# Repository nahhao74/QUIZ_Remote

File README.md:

<div align="center">

# Quiz Remote · ClassPulse

**A wireless classroom quiz system: battery-powered ESP32 answer pads, an MQTT broker and a live teacher dashboard.**

</div>

---

## Overview

Every student holds a small pad with 16 keys and two 7-segment digits. The teacher opens a session on a laptop, students type the 6-digit room code, and answers arrive on the projector within a fraction of a second. The whole system runs on the classroom Wi-Fi or a phone hotspot — no Internet connection is required.

| | |
|---|---|
| **Zero standby current** | A key press switches the board on; the ESP32 holds its own power and cuts it completely when done |
| **Reliable delivery** | MQTT QoS 1, an application-level ACK, retries and server-side de-duplication — no answer is lost or counted twice |
| **Network setup without reflashing** | Hold `0` for 3 s and the pad opens a captive-portal Wi-Fi setup page for any phone |
| **Live results** | Answer counts and the A–D distribution update in real time; correct answers stay hidden until the question closes |
| **Item analysis** | Difficulty, discrimination index, distractor effectiveness and KR-20 reliability after every session |
| **Question import** | Word, Excel, PDF and TXT, with optional AI help to write and review questions |

## The device

<table>
<tr>
<td align="center" width="28%"></td>
<td align="center" width="44%"></td>
<td align="center" width="28%"></td>
</tr>
<tr>
<td align="center"><sub>Showing a final score of 10</sub></td>
<td align="center"><sub>3D-printed enclosure, 16 keys, two 7-segment digits</sub></td>
<td align="center"><sub>Inside: the PCB and the 2 × AAA holder</sub></td>
</tr>
</table>

## The teacher app

<table>
<tr>
<td width="50%"></td>
<td width="50%"></td>
</tr>
<tr>
<td align="center"><sub>Presentation view after a question closes: correct answer, explanation and the A–D chart</sub></td>
<td align="center"><sub>Dashboard: question sets, AI assistant, exams, classes and session history</sub></td>
</tr>
<tr>
<td width="50%"></td>
<td width="50%"></td>
</tr>
<tr>
<td align="center"><sub>Session control: room code, question controls and every student's status in real time</sub></td>
<td align="center"><sub>End-of-session report: participation, accuracy and per-question results, with CSV export</sub></td>
</tr>
</table>

The interface is in Vietnamese.

## How it works

```mermaid
flowchart LR
  subgraph Classroom["Classroom LAN (Wi-Fi 2.4 GHz)"]
    P1[ESP32 pad]:::dev
    P2[ESP32 pad]:::dev
    P3[ESP32 pad ×N]:::dev
  end
  subgraph Laptop["Teacher laptop · Docker Compose"]
    M[(EMQX<br/>MQTT broker)]
    B[NestJS<br/>backend]
    D[(PostgreSQL)]
    W[React<br/>teacher app]
  end
  P1 & P2 & P3 -- "join / answer<br/>QoS 1" --> M
  M -- "ACK + retained room state" --> P1 & P2 & P3
  M <--> B
  B -- transaction --> D
  B -- Socket.IO --> W
  W -- REST --> B
  classDef dev fill:#fde7e4,stroke:#e7352c
```

One answer, end to end:

```mermaid
sequenceDiagram
  autonumber
  participant S as Student pad
  participant M as EMQX
  participant B as Backend
  participant D as PostgreSQL
  participant T as Teacher screen
  S->>M: answer (requestId, questionId, B, sequence)
  M->>B: deliver (QoS 1)
  B->>D: check room, deadline and sequence, then save answer and requestId in one transaction
  B-->>M: ack ANSWER_ACCEPTED
  M-->>S: ack (same requestId)
  B-->>T: session:update (counts, chart)
  Note over S,B: No ACK within 4 s → resend the identical message (up to 3 times).<br/>A repeated requestId returns the original result instead of saving twice.
```

## Hardware

<table>
<tr><td>

| Block | Function |
|---|---|
| **M1** | 2 × AAA cells, slide switch |
| **M2** | P-MOSFET power gate: key-press wake, GPIO13 self-hold |
| **M3** | MT3608 boost to 3.37 V on the 3V3 pin |
| **M4** | ESP32-WROOM-32 module in sockets |
| **M5** | 4 × 4 keypad (16 keys), also wakes the board |
| **M6** | 74HC595 + two 7-segment digits, multiplexed every 2 ms |

</td><td>

</td></tr>
</table>

<p align="center">&nbsp;&nbsp;&nbsp;<br><sub>The 52 × 90 mm two-layer board, front and back.</sub></p>

Schematic sheets, PCB, Gerber files, BOM and the full design rationale are in [`hardware/`](hardware/README.md) and the [design document](hardware/docs/design-document.md).

### What the digits show

| LED | Meaning | | LED | Meaning |
|:---:|---|---|:---:|---|
| `88` | Boot self-test | | `E1` | No Wi-Fi |
| `Ph` | Enter the room code | | `E2` | MQTT not connected |
| `Id` | Enter the student code | | `E3` | Rejected by the server |
| `On` | Connected to the server | | `E4` | Wrong number of digits |
| `01` | Question number | | `CF` | Wi-Fi setup page open |
| `A`…`d` | Selected answer | | `OF` | Powering off |

**Keys:** `1`–`4` choose A–D · `#` confirms · `*` deletes, or held 3 s powers off · `0` held 3 s opens Wi-Fi setup.

## Results

Measured with 50 simulated devices joining and answering at the same time, through the same broker and protocol as the real pads:

| Joined | Answers saved | Rejected / timed out | Duplicates saved twice | ACK latency p50 | p95 | max |
|:---:|:---:|:---:|:---:|:---:|:---:|:---:|
| **50 / 50** | **50 / 50** | **0** | **0** of 100 | **181 ms** | **371 ms** | **405 ms** |

The assembled board has completed a full quiz on two AAA cells over a phone hotspot. Full test report: [`web/docs/testing.md`](web/docs/testing.md).

## Repository layout

```text
.
├── hardware/                 KiCad 10 project, schematic PDFs/PNGs, Gerber, BOM, design document
│   ├── compact/              The current 52 × 90 mm board
│   ├── docs/                 Design document
│   └── tools/                PCB build script, ngspice wake/hold simulation, Wokwi sketch
├── firmware/                 Arduino sketches for the ESP32
│   ├── ClassPulseQuizDevice/       The quiz pad firmware (Wi-Fi, MQTT, power control, setup portal)
│   ├── ClassPulseKeypadDisplay/    Bring-up test: keypad → digits
│   └── ClassPulsePcbBreadboardTest/  Bring-up test: power latch, keys, segments, Wi-Fi
└── web/                      Server side, run with Docker Compose
    ├── apps/backend/         NestJS · Prisma · MQTT subscriber · REST · Socket.IO
    ├── apps/frontend/        React + Tailwind teacher app and presentation view
    ├── apps/device-simulator/  Browser pad simulator (MQTT over WebSocket)
    ├── packages/             Shared types and MQTT contracts (Zod)
    └── docs/                 Architecture, MQTT protocol, API, test report
```

## Quick start

**1. Server** (Docker with Compose v2):

```bash
cd web
cp .env.example .env          # fill in the <...> values
# set MQTT_TCP_BIND_ADDRESS to the laptop's Wi-Fi IP (hostname -I)
docker compose up --build -d
docker compose exec backend pnpm db:seed
```

Open **http://localhost:8080** and log in with the development account from the seed (see [`web/README.md`](web/README.md)).

**2. Device** (Arduino IDE, board *ESP32 Dev Module*): open `firmware/ClassPulseQuizDevice/ClassPulseQuizDevice.ino`, set `WIFI_SSID`, `WIFI_PASSWORD` and `MQTT_HOST` (the laptop's IP), then upload.

**3. Run a quiz:** start a session on the web → on the pad enter the room code `#`, a 2-digit student code `#` → answer with `1`–`4` and `#`.

> [!TIP]
> No spare pads? Add 30 simulated students to the same room:
> ```bash
> docker compose exec -e MQTT_URL=mqtt://emqx:1883 backend pnpm simulate --devices=30 --room=<room code>
> ```

> [!NOTE]
> The ESP32 only supports **2.4 GHz** Wi-Fi, and the pads and the laptop must be on the same network.

## Documentation

| Topic | Document |
|---|---|
| Board design, calculations, BOM | [hardware/README.md](hardware/README.md) · [design-document.md](hardware/docs/design-document.md) |
| Firmware configuration and usage | [firmware/ClassPulseQuizDevice/README.md](firmware/ClassPulseQuizDevice/README.md) |
| Server setup and features | [web/README.md](web/README.md) |
| System architecture and data model | [web/docs/architecture.md](web/docs/architecture.md) |
| MQTT topics, payloads, ACK codes | [web/docs/mqtt-protocol.md](web/docs/mqtt-protocol.md) |
| REST API and Socket.IO | [web/docs/api.md](web/docs/api.md) |
| Test report | [web/docs/testing.md](web/docs/testing.md) |

## License

Released under the [MIT License](LICENSE).

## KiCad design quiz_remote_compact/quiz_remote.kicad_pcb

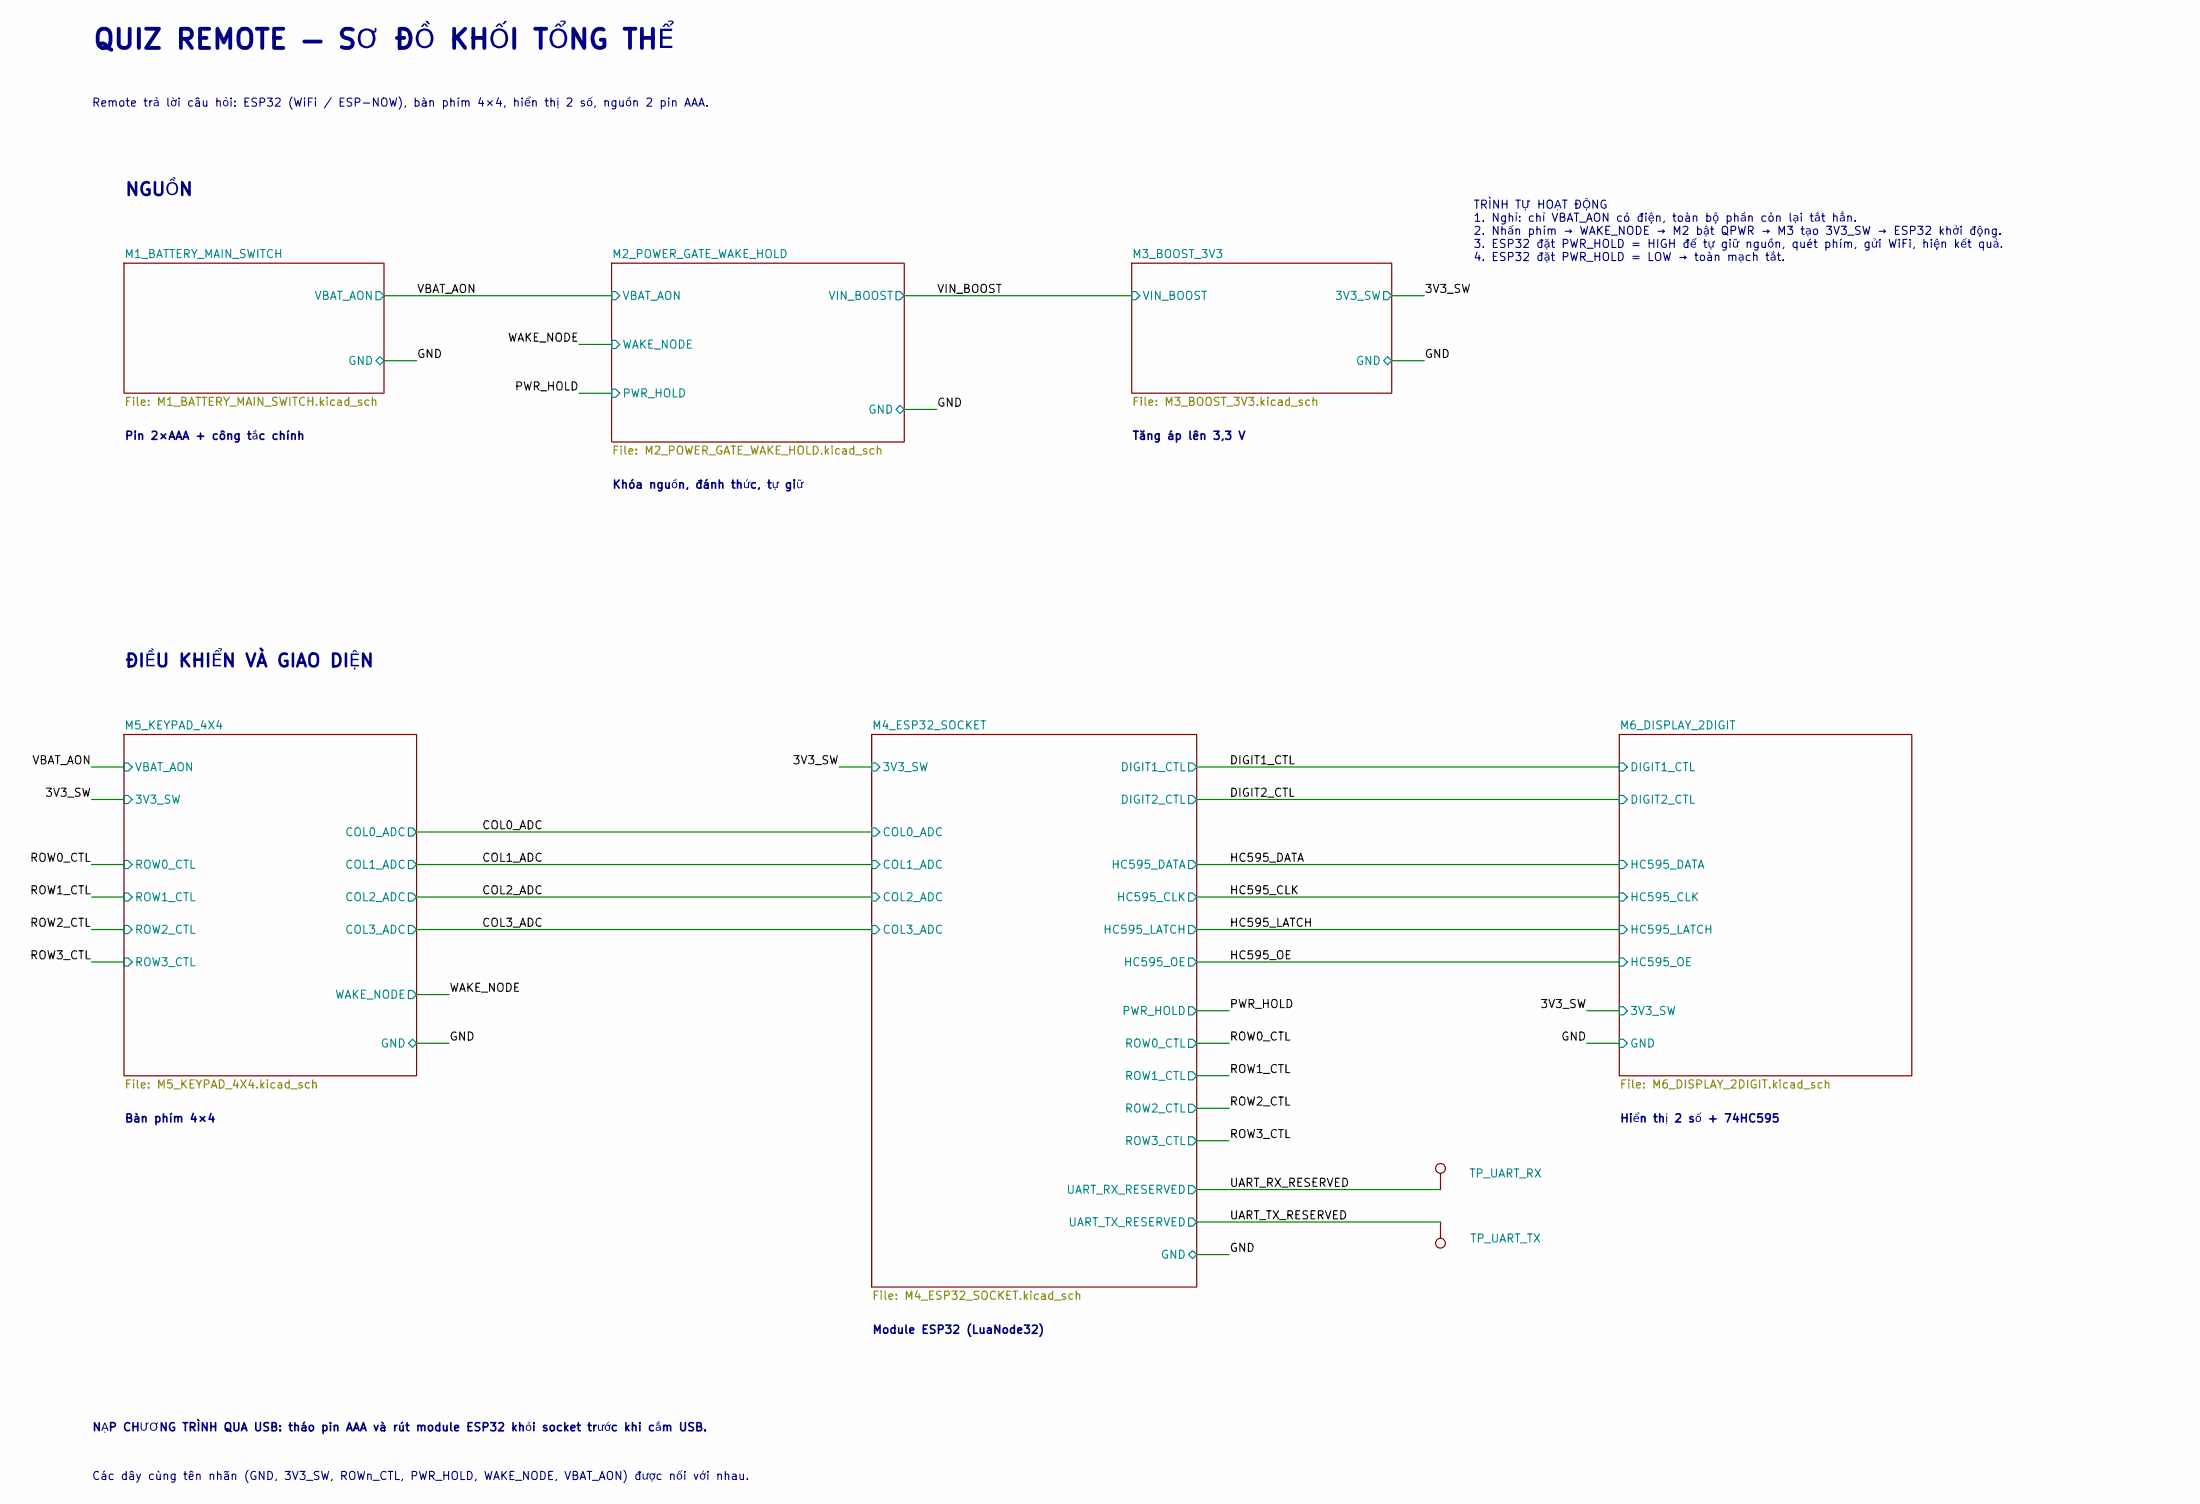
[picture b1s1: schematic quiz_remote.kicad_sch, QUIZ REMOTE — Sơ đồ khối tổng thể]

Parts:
TP_UART_RX: UART_RX_RESERVED; TestPoint_Pad_D1.5mm
TP_UART_TX: UART_TX_RESERVED; TestPoint_Pad_D1.5mm

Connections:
/UART_RX_RESERVED: TP_UART_RX.1; also elsewhere on the board
/UART_TX_RESERVED: TP_UART_TX.1; also elsewhere on the board

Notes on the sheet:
Pin 2×AAA + công tắc chính
Khóa nguồn, đánh thức, tự giữ
Tăng áp lên 3,3 V
Bàn phím 4×4
Module ESP32 (LuaNode32)
Hiển thị 2 số + 74HC595
QUIZ REMOTE — SƠ ĐỒ KHỐI TỔNG THỂ
Remote trả lời câu hỏi: ESP32 (WiFi / ESP-NOW), bàn phím 4×4, hiển thị 2 số, nguồn 2 pin AAA.
NGUỒN
ĐIỀU KHIỂN VÀ GIAO DIỆN
TRÌNH TỰ HOẠT ĐỘNG 1. Nghỉ: chỉ VBAT_AON có điện, toàn bộ phần còn lại tắt hẳn. 2. Nhấn phím → WAKE_NODE → M2 bật QPWR → M3 tạo 3V3_SW → ESP32 khởi động. 3. ESP32 đặt PWR_HOLD = HIGH để tự giữ nguồn, quét phím, gửi WiFi, hiện kết quả. 4. ESP32 đặt PWR_HOLD = LOW → toàn mạch tắt.
NẠP CHƯƠNG TRÌNH QUA USB: tháo pin AAA và rút module ESP32 khỏi socket trước khi cắm USB.
Các dây cùng tên nhãn (GND, 3V3_SW, ROWn_CTL, PWR_HOLD, WAKE_NODE, VBAT_AON) được nối với nhau.

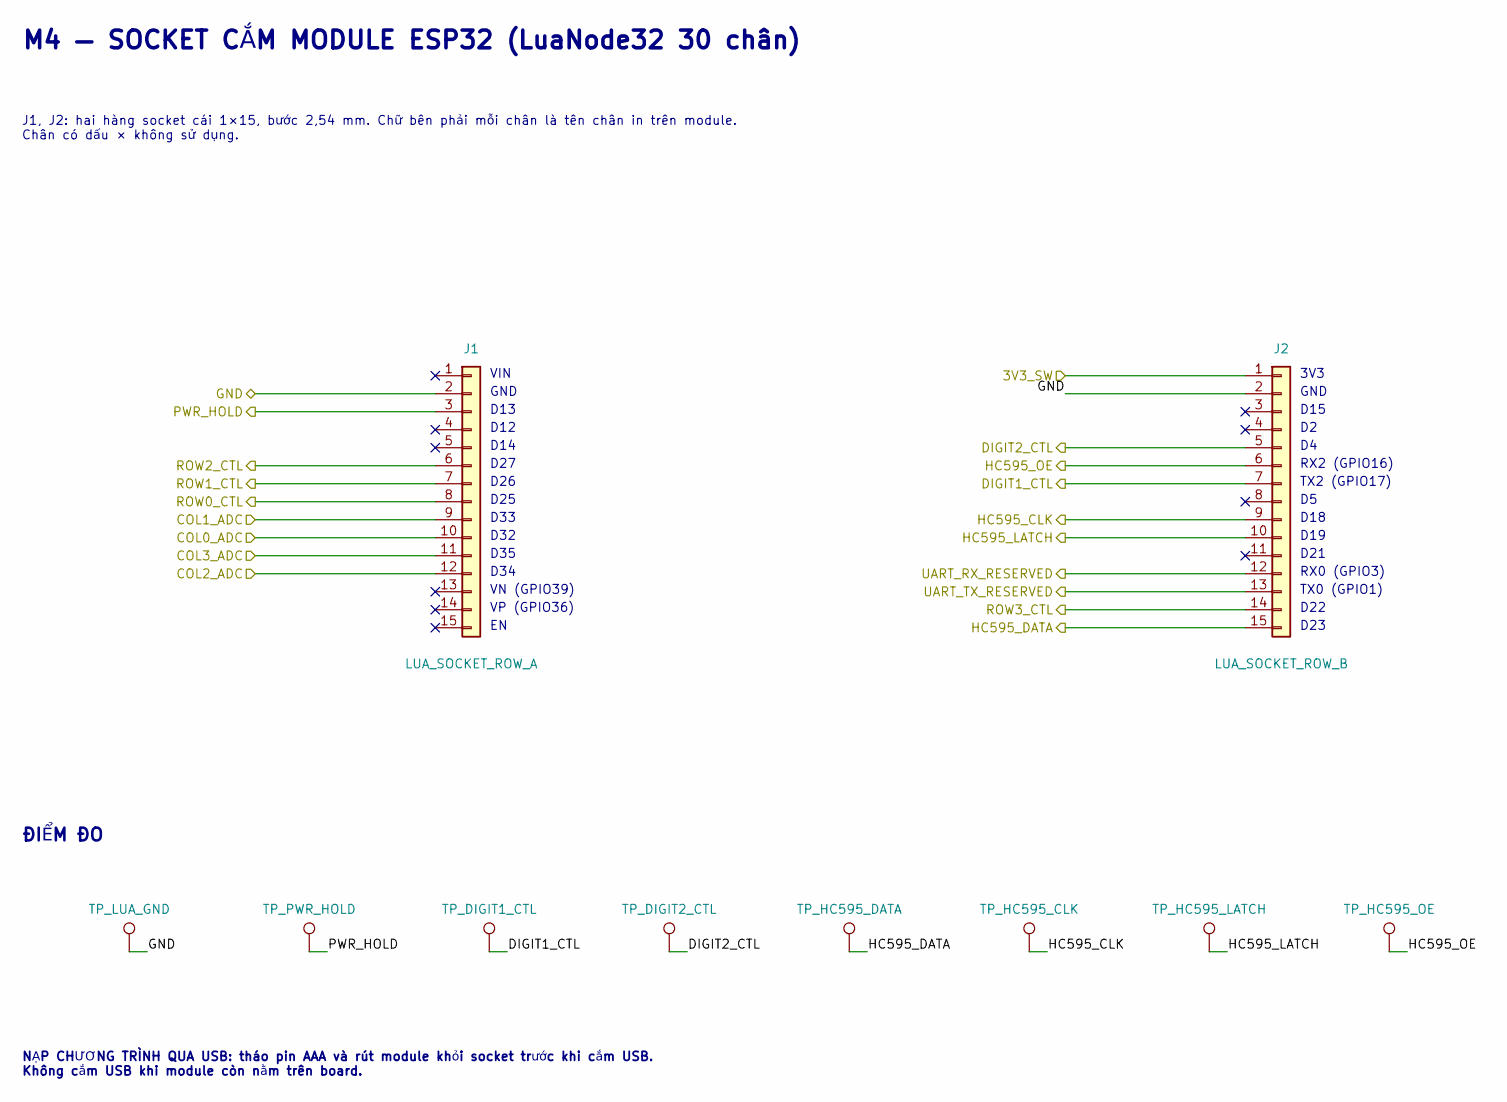
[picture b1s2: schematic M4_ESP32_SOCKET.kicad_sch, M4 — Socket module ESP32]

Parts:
J1: LUA_SOCKET_ROW_A; PinSocket_1x15_P2.54mm_Vertical; MPN 1x40_female_2.54_11.8_cut15
J2: LUA_SOCKET_ROW_B; PinSocket_1x15_P2.54mm_Vertical; MPN 1x40_female_2.54_11.8_cut15
TP_DIGIT1_CTL: DIGIT1_CTL; TestPoint_Pad_D1.5mm
TP_DIGIT2_CTL: DIGIT2_CTL; TestPoint_Pad_D1.5mm
TP_HC595_CLK: HC595_CLK; TestPoint_Pad_D1.5mm
TP_HC595_DATA: HC595_DATA; TestPoint_Pad_D1.5mm
TP_HC595_LATCH: HC595_LATCH; TestPoint_Pad_D1.5mm
TP_HC595_OE: HC595_OE; TestPoint_Pad_D1.5mm
TP_LUA_GND: GND; TestPoint_Pad_D1.5mm
TP_PWR_HOLD: PWR_HOLD; TestPoint_Pad_D1.5mm

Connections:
/3V3_SW: J2.1; also elsewhere on the board
/COL0_ADC: J1.10; also elsewhere on the board
/COL1_ADC: J1.9; also elsewhere on the board
/COL2_ADC: J1.12; also elsewhere on the board
/COL3_ADC: J1.11; also elsewhere on the board
/DIGIT1_CTL: J2.7, TP_DIGIT1_CTL.1; also elsewhere on the board
/DIGIT2_CTL: J2.5, TP_DIGIT2_CTL.1; also elsewhere on the board
/HC595_CLK: J2.9, TP_HC595_CLK.1; also elsewhere on the board
/HC595_DATA: J2.15, TP_HC595_DATA.1; also elsewhere on the board
/HC595_LATCH: J2.10, TP_HC595_LATCH.1; also elsewhere on the board
/HC595_OE: J2.6, TP_HC595_OE.1; also elsewhere on the board
/PWR_HOLD: J1.3, TP_PWR_HOLD.1; also elsewhere on the board
/ROW0_CTL: J1.8; also elsewhere on the board
/ROW1_CTL: J1.7; also elsewhere on the board
/ROW2_CTL: J1.6; also elsewhere on the board
/ROW3_CTL: J2.14; also elsewhere on the board
/UART_RX_RESERVED: J2.12; also elsewhere on the board
/UART_TX_RESERVED: J2.13; also elsewhere on the board

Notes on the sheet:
VIN
GND
D13
D12
D14
D27
D26
D25
D33
D32
D35
D34
VN (GPIO39)
VP (GPIO36)
3V3
D15
RX2 (GPIO16)
TX2 (GPIO17)
D18
D19
D21
RX0 (GPIO3)
TX0 (GPIO1)
D22
D23
M4 — SOCKET CẮM MODULE ESP32 (LuaNode32 30 chân)
J1, J2: hai hàng socket cái 1×15, bước 2,54 mm. Chữ bên phải mỗi chân là tên chân in trên module. Chân có dấu × không sử dụng.
ĐIỂM ĐO
NẠP CHƯƠNG TRÌNH QUA USB: tháo pin AAA và rút module khỏi socket trước khi cắm USB. Không cắm USB khi module còn nằm trên board.

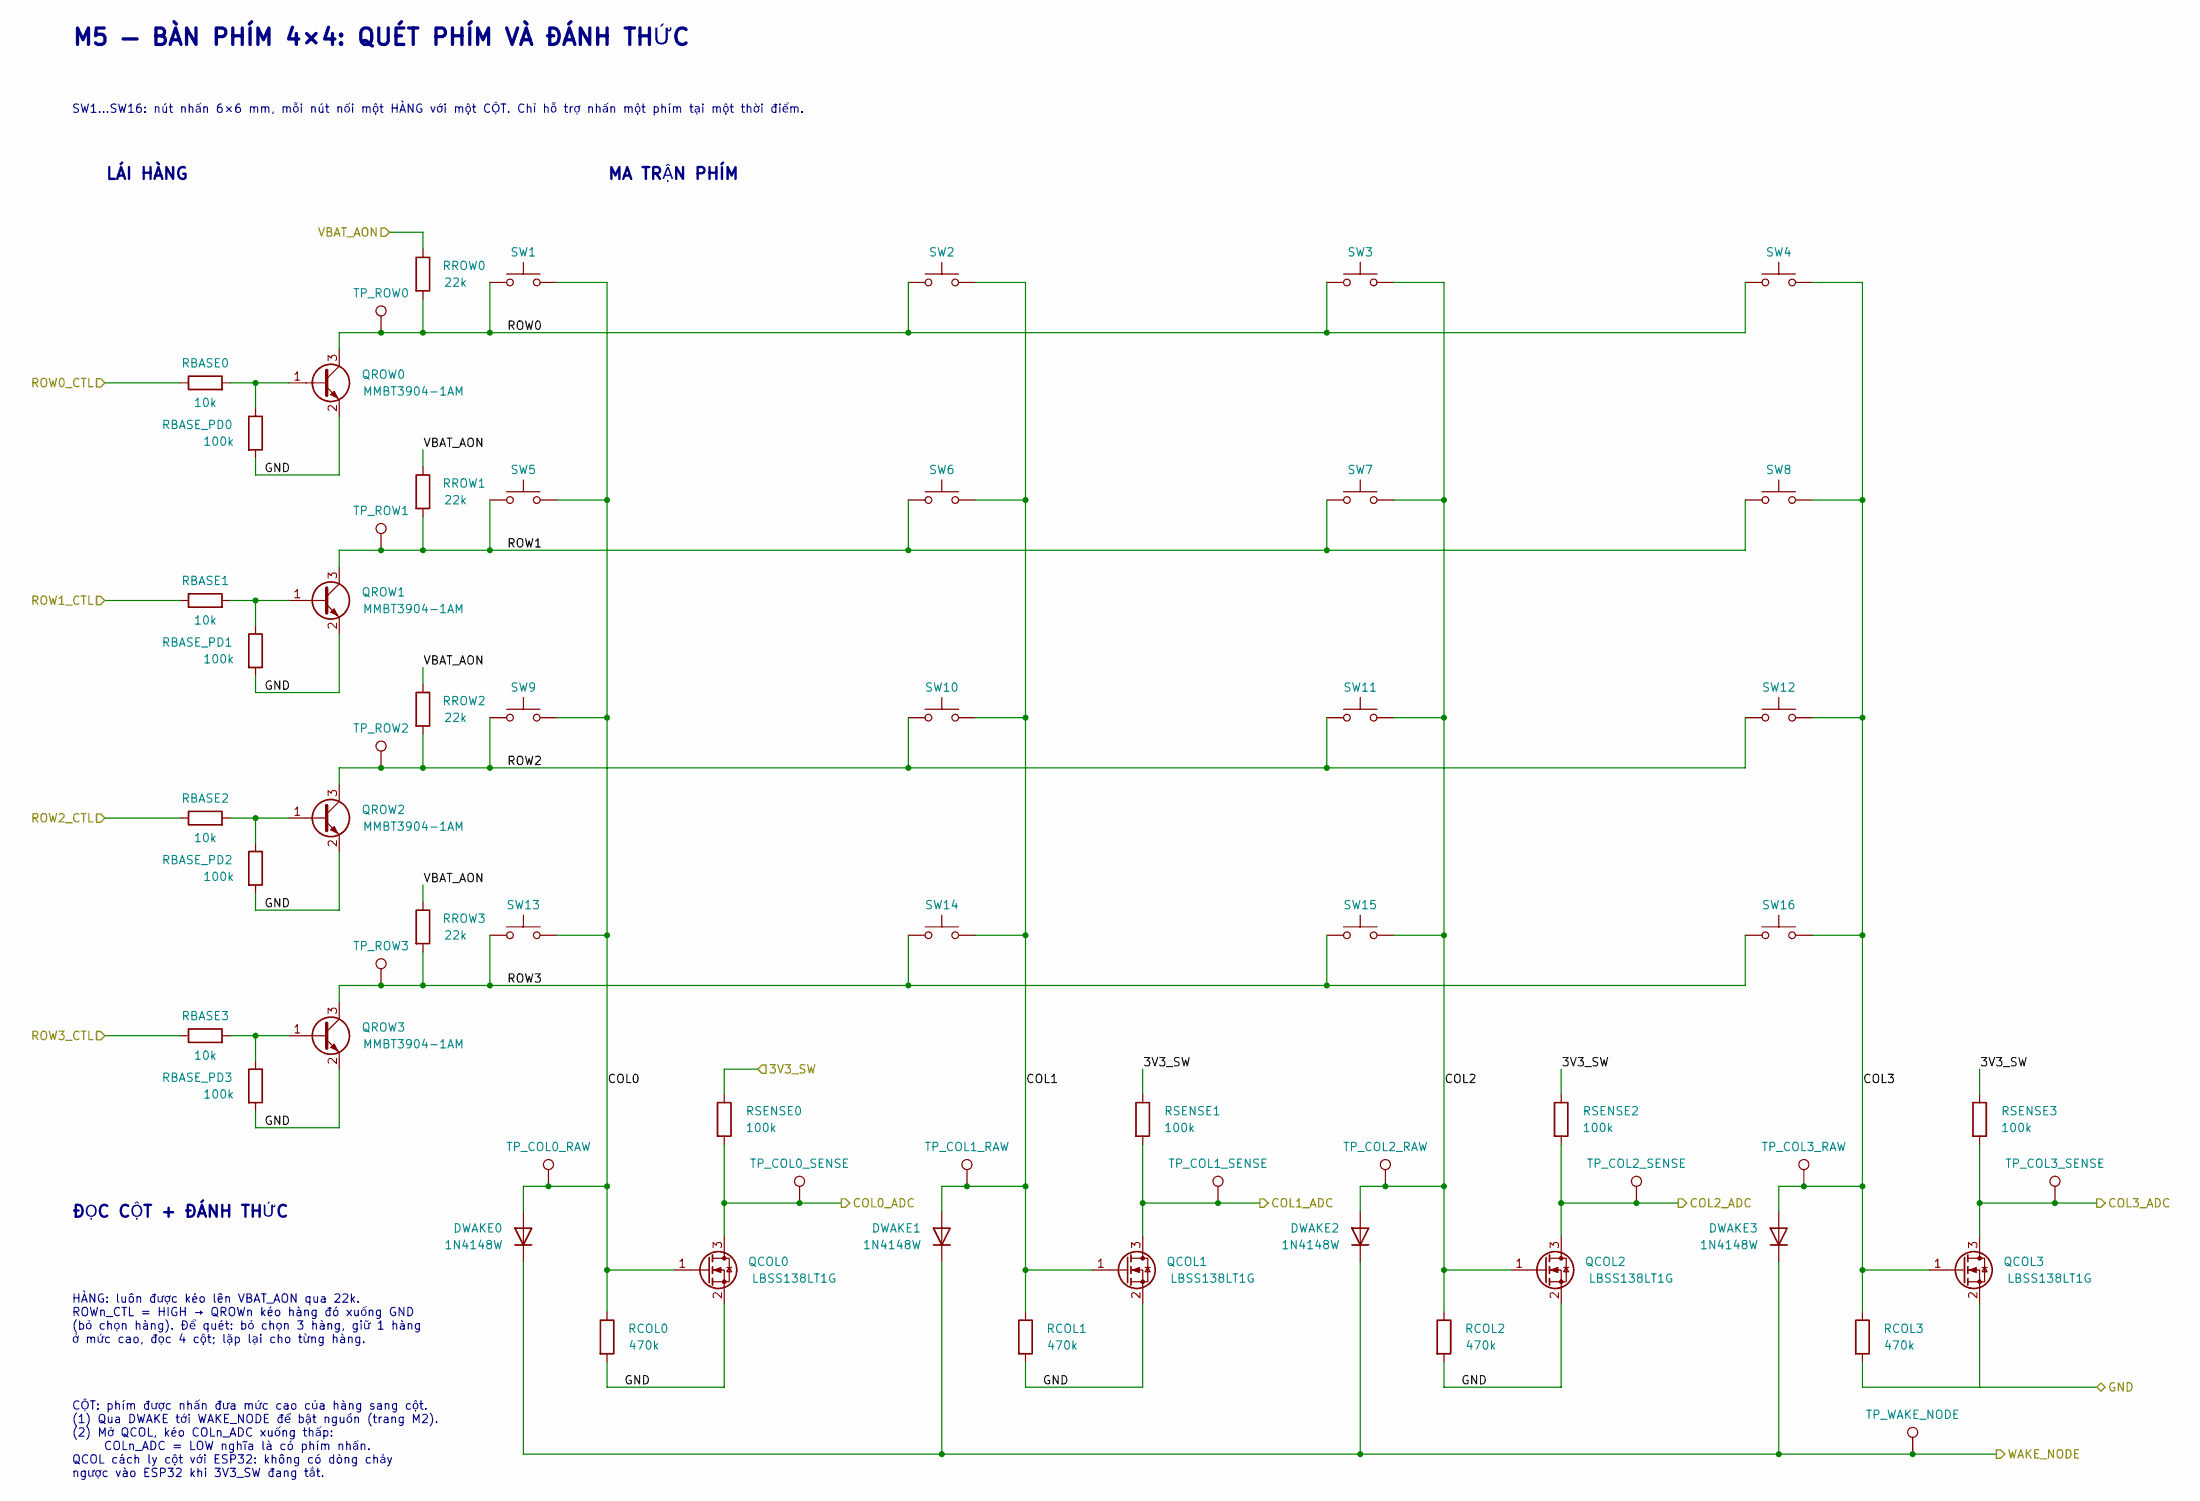
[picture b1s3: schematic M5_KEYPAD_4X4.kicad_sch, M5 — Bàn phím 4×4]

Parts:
DWAKE0, DWAKE1, DWAKE2, DWAKE3: 1N4148W; D_SOD-123; MPN 1N4148W-E3-18
QCOL0, QCOL1, QCOL2, QCOL3: LBSS138LT1G; SOT-23; MPN LBSS138LT1G
QROW0, QROW1, QROW2, QROW3: MMBT3904-1AM; SOT-23; MPN MMBT3904,215
RBASE0, RBASE1, RBASE2, RBASE3: 10k; R_0805_2012Metric; MPN RC0805FR-0710KL
RBASE_PD0, RBASE_PD1, RBASE_PD2, RBASE_PD3: 100k; R_0805_2012Metric; MPN RC0805FR-07100KL
RCOL0, RCOL1, RCOL2, RCOL3: 470k; R_0805_2012Metric; MPN RC0805FR-07470KL
RROW0, RROW1, RROW2, RROW3: 22k; R_0805_2012Metric; MPN RC0805FR-0722KL
RSENSE0, RSENSE1, RSENSE2, RSENSE3: 100k; R_0805_2012Metric; MPN RC0805FR-07100KL
SW1, SW2, SW3, SW4, SW5, SW6, SW7, SW8, SW9, SW10, SW11, SW12, SW13, SW14, SW15, SW16: 6x6_THT_NO; SW_6x6_H4.3_LK14489; MPN LK14489
TP_COL0_RAW: COL0; TestPoint_Pad_D1.5mm
TP_COL0_SENSE: COL0_ADC; TestPoint_Pad_D1.5mm
TP_COL1_RAW: COL1; TestPoint_Pad_D1.5mm
TP_COL1_SENSE: COL1_ADC; TestPoint_Pad_D1.5mm
TP_COL2_RAW: COL2; TestPoint_Pad_D1.5mm
TP_COL2_SENSE: COL2_ADC; TestPoint_Pad_D1.5mm
TP_COL3_RAW: COL3; TestPoint_Pad_D1.5mm
TP_COL3_SENSE: COL3_ADC; TestPoint_Pad_D1.5mm
TP_ROW0: ROW0; TestPoint_Pad_D1.5mm
TP_ROW1: ROW1; TestPoint_Pad_D1.5mm
TP_ROW2: ROW2; TestPoint_Pad_D1.5mm
TP_ROW3: ROW3; TestPoint_Pad_D1.5mm
TP_WAKE_NODE: WAKE_NODE; TestPoint_Pad_D1.5mm

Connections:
/3V3_SW: RSENSE0.1, RSENSE1.1, RSENSE2.1, RSENSE3.1; also elsewhere on the board
/COL0_ADC: QCOL0.3 (D), RSENSE0.2, TP_COL0_SENSE.1; also elsewhere on the board
/COL1_ADC: QCOL1.3 (D), RSENSE1.2, TP_COL1_SENSE.1; also elsewhere on the board
/COL2_ADC: QCOL2.3 (D), RSENSE2.2, TP_COL2_SENSE.1; also elsewhere on the board
/COL3_ADC: QCOL3.3 (D), RSENSE3.2, TP_COL3_SENSE.1; also elsewhere on the board
/M5_KEYPAD_4X4/COL0: DWAKE0.2 (A), QCOL0.1 (G), RCOL0.1, SW1.2, SW5.2, SW9.2, SW13.2, TP_COL0_RAW.1
/M5_KEYPAD_4X4/COL1: DWAKE1.2 (A), QCOL1.1 (G), RCOL1.1, SW2.2, SW6.2, SW10.2, SW14.2, TP_COL1_RAW.1
/M5_KEYPAD_4X4/COL2: DWAKE2.2 (A), QCOL2.1 (G), RCOL2.1, SW3.2, SW7.2, SW11.2, SW15.2, TP_COL2_RAW.1
/M5_KEYPAD_4X4/COL3: DWAKE3.2 (A), QCOL3.1 (G), RCOL3.1, SW4.2, SW8.2, SW12.2, SW16.2, TP_COL3_RAW.1
/M5_KEYPAD_4X4/ROW0: QROW0.3 (C), RROW0.2, SW1.1, SW2.1, SW3.1, SW4.1, TP_ROW0.1
/M5_KEYPAD_4X4/ROW1: QROW1.3 (C), RROW1.2, SW5.1, SW6.1, SW7.1, SW8.1, TP_ROW1.1
/M5_KEYPAD_4X4/ROW2: QROW2.3 (C), RROW2.2, SW9.1, SW10.1, SW11.1, SW12.1, TP_ROW2.1
/M5_KEYPAD_4X4/ROW3: QROW3.3 (C), RROW3.2, SW13.1, SW14.1, SW15.1, SW16.1, TP_ROW3.1
/ROW0_CTL: RBASE0.1; also elsewhere on the board
/ROW1_CTL: RBASE1.1; also elsewhere on the board
/ROW2_CTL: RBASE2.1; also elsewhere on the board
/ROW3_CTL: RBASE3.1; also elsewhere on the board
/VBAT_AON: RROW0.1, RROW1.1, RROW2.1, RROW3.1; also elsewhere on the board
/WAKE_NODE: DWAKE0.1 (K), DWAKE1.1 (K), DWAKE2.1 (K), DWAKE3.1 (K), TP_WAKE_NODE.1; also elsewhere on the board
unnamed: QROW0.1 (B), RBASE0.2, RBASE_PD0.1
unnamed: QROW1.1 (B), RBASE1.2, RBASE_PD1.1
unnamed: QROW2.1 (B), RBASE2.2, RBASE_PD2.1
unnamed: QROW3.1 (B), RBASE3.2, RBASE_PD3.1

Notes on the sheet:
M5 — BÀN PHÍM 4×4: QUÉT PHÍM VÀ ĐÁNH THỨC
SW1…SW16: nút nhấn 6×6 mm, mỗi nút nối một HÀNG với một CỘT. Chỉ hỗ trợ nhấn một phím tại một thời điểm.
LÁI HÀNG
MA TRẬN PHÍM
ĐỌC CỘT + ĐÁNH THỨC
HÀNG: luôn được kéo lên VBAT_AON qua 22k. ROWn_CTL = HIGH → QROWn kéo hàng đó xuống GND (bỏ chọn hàng). Để quét: bỏ chọn 3 hàng, giữ 1 hàng ở mức cao, đọc 4 cột; lặp lại cho từng hàng.
CỘT: phím được nhấn đưa mức cao của hàng sang cột. (1) Qua DWAKE tới WAKE_NODE để bật nguồn (trang M2). (2) Mở QCOL, kéo COLn_ADC xuống thấp: COLn_ADC = LOW nghĩa là có phím nhấn. QCOL cách ly cột với ESP32: không có dòng chảy ngược vào ESP32 khi 3V3_SW đang tắt.

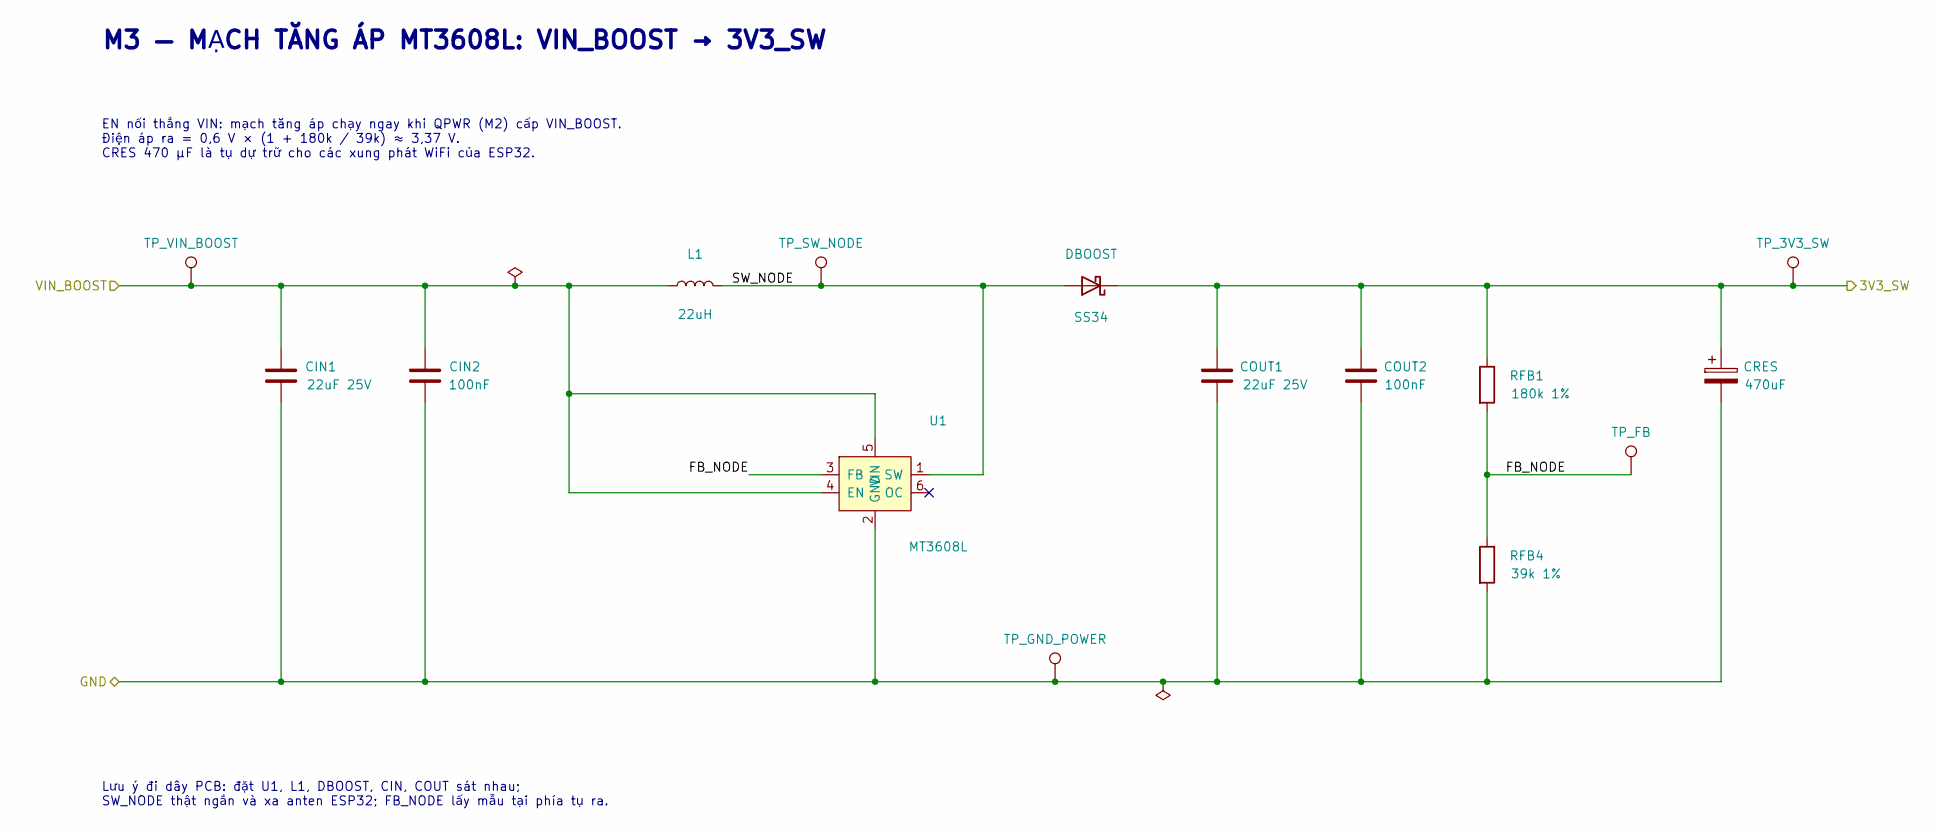
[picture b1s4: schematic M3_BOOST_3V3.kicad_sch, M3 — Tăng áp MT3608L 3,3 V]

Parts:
CIN1: 22uF 25V; C_1210_3225Metric; Ratings 22uF25V1210; vendorSKUidentityonly; eff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; MPN Supplier_22uF_25V_1210
CIN2: 100nF; C_0805_2012Metric; Ratings 100nF +/-10%,50V,X7R,0805; prototype ha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; MPN C0805C104K5RACTU
COUT1: 22uF 25V; C_1210_3225Metric; Ratings 22uF25V1210; vendorSKUidentityonly; eff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; MPN Supplier_22uF_25V_1210
COUT2: 100nF; C_0805_2012Metric; Ratings 100nF +/-10%,50V,X7R,0805; prototype ha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; MPN C0805C104K5RACTU
CRES: 470uF; CRES_IC4172_D8_P3.50_Prototype; Ratings 470uF16V+/-20%,D8H12.5P3.5; noESRinferr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; MPN IC4172_supplier_identity_NO_exact_MPN
DBOOST: SS34; D_SMC; MPN SS34-E3/57T
L1: 22uH; L_8D43_220_ThegioiIC; Ratings 22uH3.25Alisted;protoaccepted; drawingt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; MPN 8D43-220
RFB1: 180k 1%; R_0805_2012Metric; MPN RC0805FR-07180KL
RFB4: 39k 1%; R_0805_2012Metric; MPN RC0805FR-0739KL
TP_3V3_SW: 3V3_SW; TestPoint_Pad_D1.5mm
TP_FB: FB_NODE; TestPoint_Pad_D1.5mm
TP_GND_POWER: GND; TestPoint_Pad_D1.5mm
TP_SW_NODE: SW_NODE; TestPoint_Pad_D1.5mm
TP_VIN_BOOST: VIN_BOOST; TestPoint_Pad_D1.5mm
U1: MT3608L; SOT-23-6; MPN MT3608L

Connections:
/3V3_SW: COUT1.1, COUT2.1, CRES.1, DBOOST.1 (K), RFB1.1, TP_3V3_SW.1; also elsewhere on the board
/M3_BOOST_3V3/FB_NODE: RFB1.2, RFB4.1, TP_FB.1, U1.3 (FB)
/M3_BOOST_3V3/SW_NODE: DBOOST.2 (A), L1.2, TP_SW_NODE.1, U1.1 (SW)

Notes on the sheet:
M3 — MẠCH TĂNG ÁP MT3608L: VIN_BOOST → 3V3_SW
EN nối thẳng VIN: mạch tăng áp chạy ngay khi QPWR (M2) cấp VIN_BOOST. Điện áp ra = 0,6 V × (1 + 180k / 39k) ≈ 3,37 V. CRES 470 µF là tụ dự trữ cho các xung phát WiFi của ESP32.
Lưu ý đi dây PCB: đặt U1, L1, DBOOST, CIN, COUT sát nhau; SW_NODE thật ngắn và xa anten ESP32; FB_NODE lấy mẫu tại phía tụ ra.

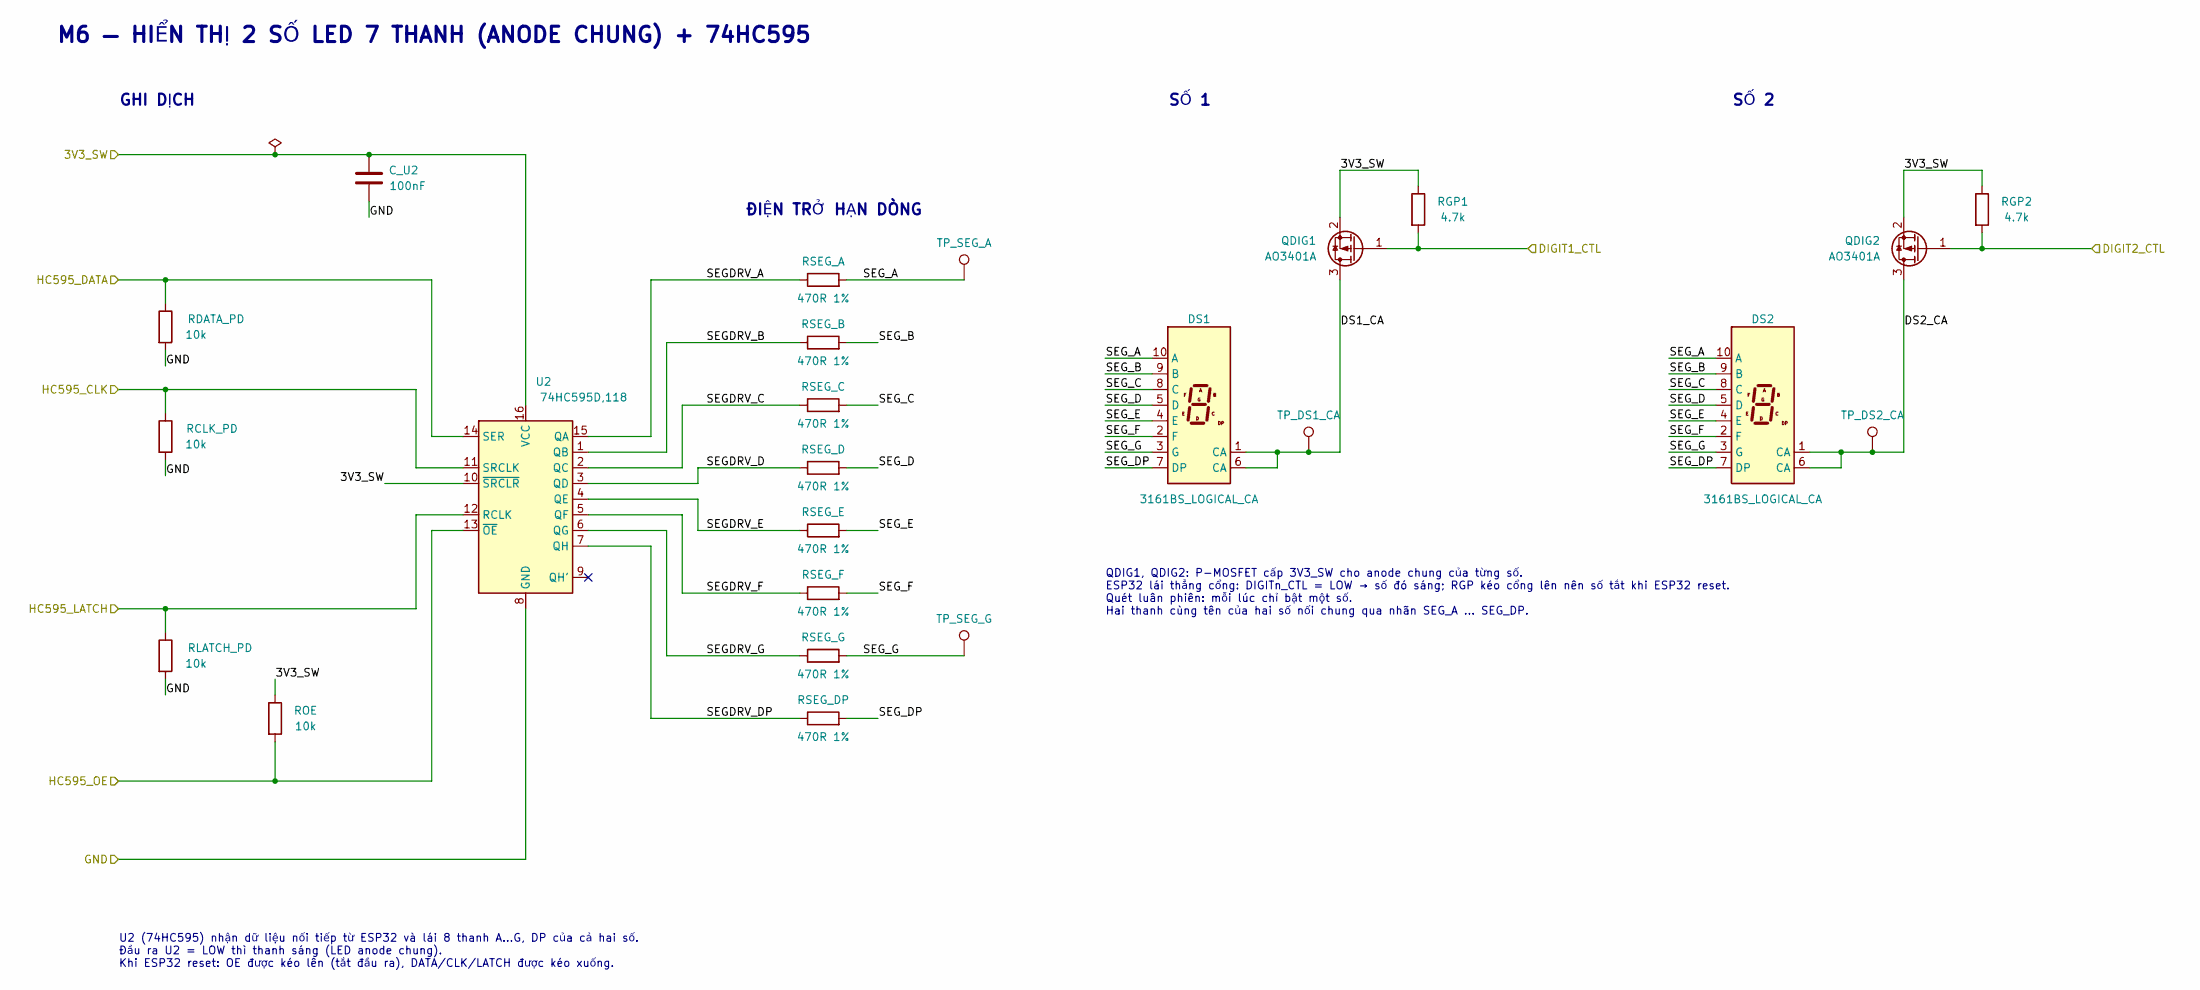
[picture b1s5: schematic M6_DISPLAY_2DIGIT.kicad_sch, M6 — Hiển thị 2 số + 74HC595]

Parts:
C_U2: 100nF; C_0805_2012Metric; Ratings 100nF +/-10%,50V,X7R,0805; prototype ha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; MPN C0805C104K5RACTU
DS1, DS2: 3161BS_LOGICAL_CA; Display_XLITX_3161BS; MPN 3161BS
QDIG1, QDIG2: AO3401A; SOT-23; MPN AO3401A
RCLK_PD: 10k; R_0805_2012Metric; MPN RC0805FR-0710KL
RDATA_PD: 10k; R_0805_2012Metric; MPN RC0805FR-0710KL
RGP1, RGP2: 4.7k; R_0805_2012Metric; MPN RC0805FR-074K7L
RLATCH_PD: 10k; R_0805_2012Metric; MPN RC0805FR-0710KL
ROE: 10k; R_0805_2012Metric; MPN RC0805FR-0710KL
RSEG_A: 470R 1%; R_0805_2012Metric; MPN RC0805FR-07470RL
RSEG_B: 470R 1%; R_0805_2012Metric; MPN RC0805FR-07470RL
RSEG_C: 470R 1%; R_0805_2012Metric; MPN RC0805FR-07470RL
RSEG_D: 470R 1%; R_0805_2012Metric; MPN RC0805FR-07470RL
RSEG_DP: 470R 1%; R_0805_2012Metric; MPN RC0805FR-07470RL
RSEG_E: 470R 1%; R_0805_2012Metric; MPN RC0805FR-07470RL
RSEG_F: 470R 1%; R_0805_2012Metric; MPN RC0805FR-07470RL
RSEG_G: 470R 1%; R_0805_2012Metric; MPN RC0805FR-07470RL
TP_DS1_CA: TP_DS1_CA; TestPoint_Pad_D1.5mm
TP_DS2_CA: TP_DS2_CA; TestPoint_Pad_D1.5mm
TP_SEG_A: TP_SEG_A; TestPoint_Pad_D1.5mm
TP_SEG_G: TP_SEG_G; TestPoint_Pad_D1.5mm
U2: 74HC595D,118; SOIC-16_3.9x9.9mm_P1.27mm; MPN 74HC595D,118

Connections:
/3V3_SW: C_U2.1, QDIG1.2 (S), QDIG2.2 (S), RGP1.1, RGP2.1, ROE.1, U2.10 (~SRCLR), U2.16 (VCC); also elsewhere on the board
/DIGIT1_CTL: QDIG1.1 (G), RGP1.2; also elsewhere on the board
/DIGIT2_CTL: QDIG2.1 (G), RGP2.2; also elsewhere on the board
/HC595_CLK: RCLK_PD.1, U2.11 (SRCLK); also elsewhere on the board
/HC595_DATA: RDATA_PD.1, U2.14 (SER); also elsewhere on the board
/HC595_LATCH: RLATCH_PD.1, U2.12 (RCLK); also elsewhere on the board
/HC595_OE: ROE.2, U2.13 (~OE); also elsewhere on the board
/M6_DISPLAY_2DIGIT/DS1_CA: DS1.1 (CA), DS1.6 (CA), QDIG1.3 (D), TP_DS1_CA.1
/M6_DISPLAY_2DIGIT/DS2_CA: DS2.1 (CA), DS2.6 (CA), QDIG2.3 (D), TP_DS2_CA.1
/M6_DISPLAY_2DIGIT/SEGDRV_A: RSEG_A.1, U2.15 (QA)
/M6_DISPLAY_2DIGIT/SEGDRV_B: RSEG_B.1, U2.1 (QB)
/M6_DISPLAY_2DIGIT/SEGDRV_C: RSEG_C.1, U2.2 (QC)
/M6_DISPLAY_2DIGIT/SEGDRV_D: RSEG_D.1, U2.3 (QD)
/M6_DISPLAY_2DIGIT/SEGDRV_DP: RSEG_DP.1, U2.7 (QH)
/M6_DISPLAY_2DIGIT/SEGDRV_E: RSEG_E.1, U2.4 (QE)
/M6_DISPLAY_2DIGIT/SEGDRV_F: RSEG_F.1, U2.5 (QF)
/M6_DISPLAY_2DIGIT/SEGDRV_G: RSEG_G.1, U2.6 (QG)
/M6_DISPLAY_2DIGIT/SEG_A: DS1.10 (A), DS2.10 (A), RSEG_A.2, TP_SEG_A.1
/M6_DISPLAY_2DIGIT/SEG_B: DS1.9 (B), DS2.9 (B), RSEG_B.2
/M6_DISPLAY_2DIGIT/SEG_C: DS1.8 (C), DS2.8 (C), RSEG_C.2
/M6_DISPLAY_2DIGIT/SEG_D: DS1.5 (D), DS2.5 (D), RSEG_D.2
/M6_DISPLAY_2DIGIT/SEG_DP: DS1.7 (DP), DS2.7 (DP), RSEG_DP.2
/M6_DISPLAY_2DIGIT/SEG_E: DS1.4 (E), DS2.4 (E), RSEG_E.2
/M6_DISPLAY_2DIGIT/SEG_F: DS1.2 (F), DS2.2 (F), RSEG_F.2
/M6_DISPLAY_2DIGIT/SEG_G: DS1.3 (G), DS2.3 (G), RSEG_G.2, TP_SEG_G.1

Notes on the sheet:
M6 — HIỂN THỊ 2 SỐ LED 7 THANH (ANODE CHUNG) + 74HC595
GHI DỊCH
ĐIỆN TRỞ HẠN DÒNG
SỐ 1
SỐ 2
U2 (74HC595) nhận dữ liệu nối tiếp từ ESP32 và lái 8 thanh A…G, DP của cả hai số. Đầu ra U2 = LOW thì thanh sáng (LED anode chung). Khi ESP32 reset: OE được kéo lên (tắt đầu ra), DATA/CLK/LATCH được kéo xuống.
QDIG1, QDIG2: P-MOSFET cấp 3V3_SW cho anode chung của từng số. ESP32 lái thẳng cổng: DIGITn_CTL = LOW → số đó sáng; RGP kéo cổng lên nên số tắt khi ESP32 reset. Quét luân phiên: mỗi lúc chỉ bật một số. Hai thanh cùng tên của hai số nối chung qua nhãn SEG_A … SEG_DP.

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

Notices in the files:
README.md:
License: MIT
